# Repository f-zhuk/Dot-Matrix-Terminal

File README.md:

# Dot-Matrix-Terminal
Dot matrix printer driver board

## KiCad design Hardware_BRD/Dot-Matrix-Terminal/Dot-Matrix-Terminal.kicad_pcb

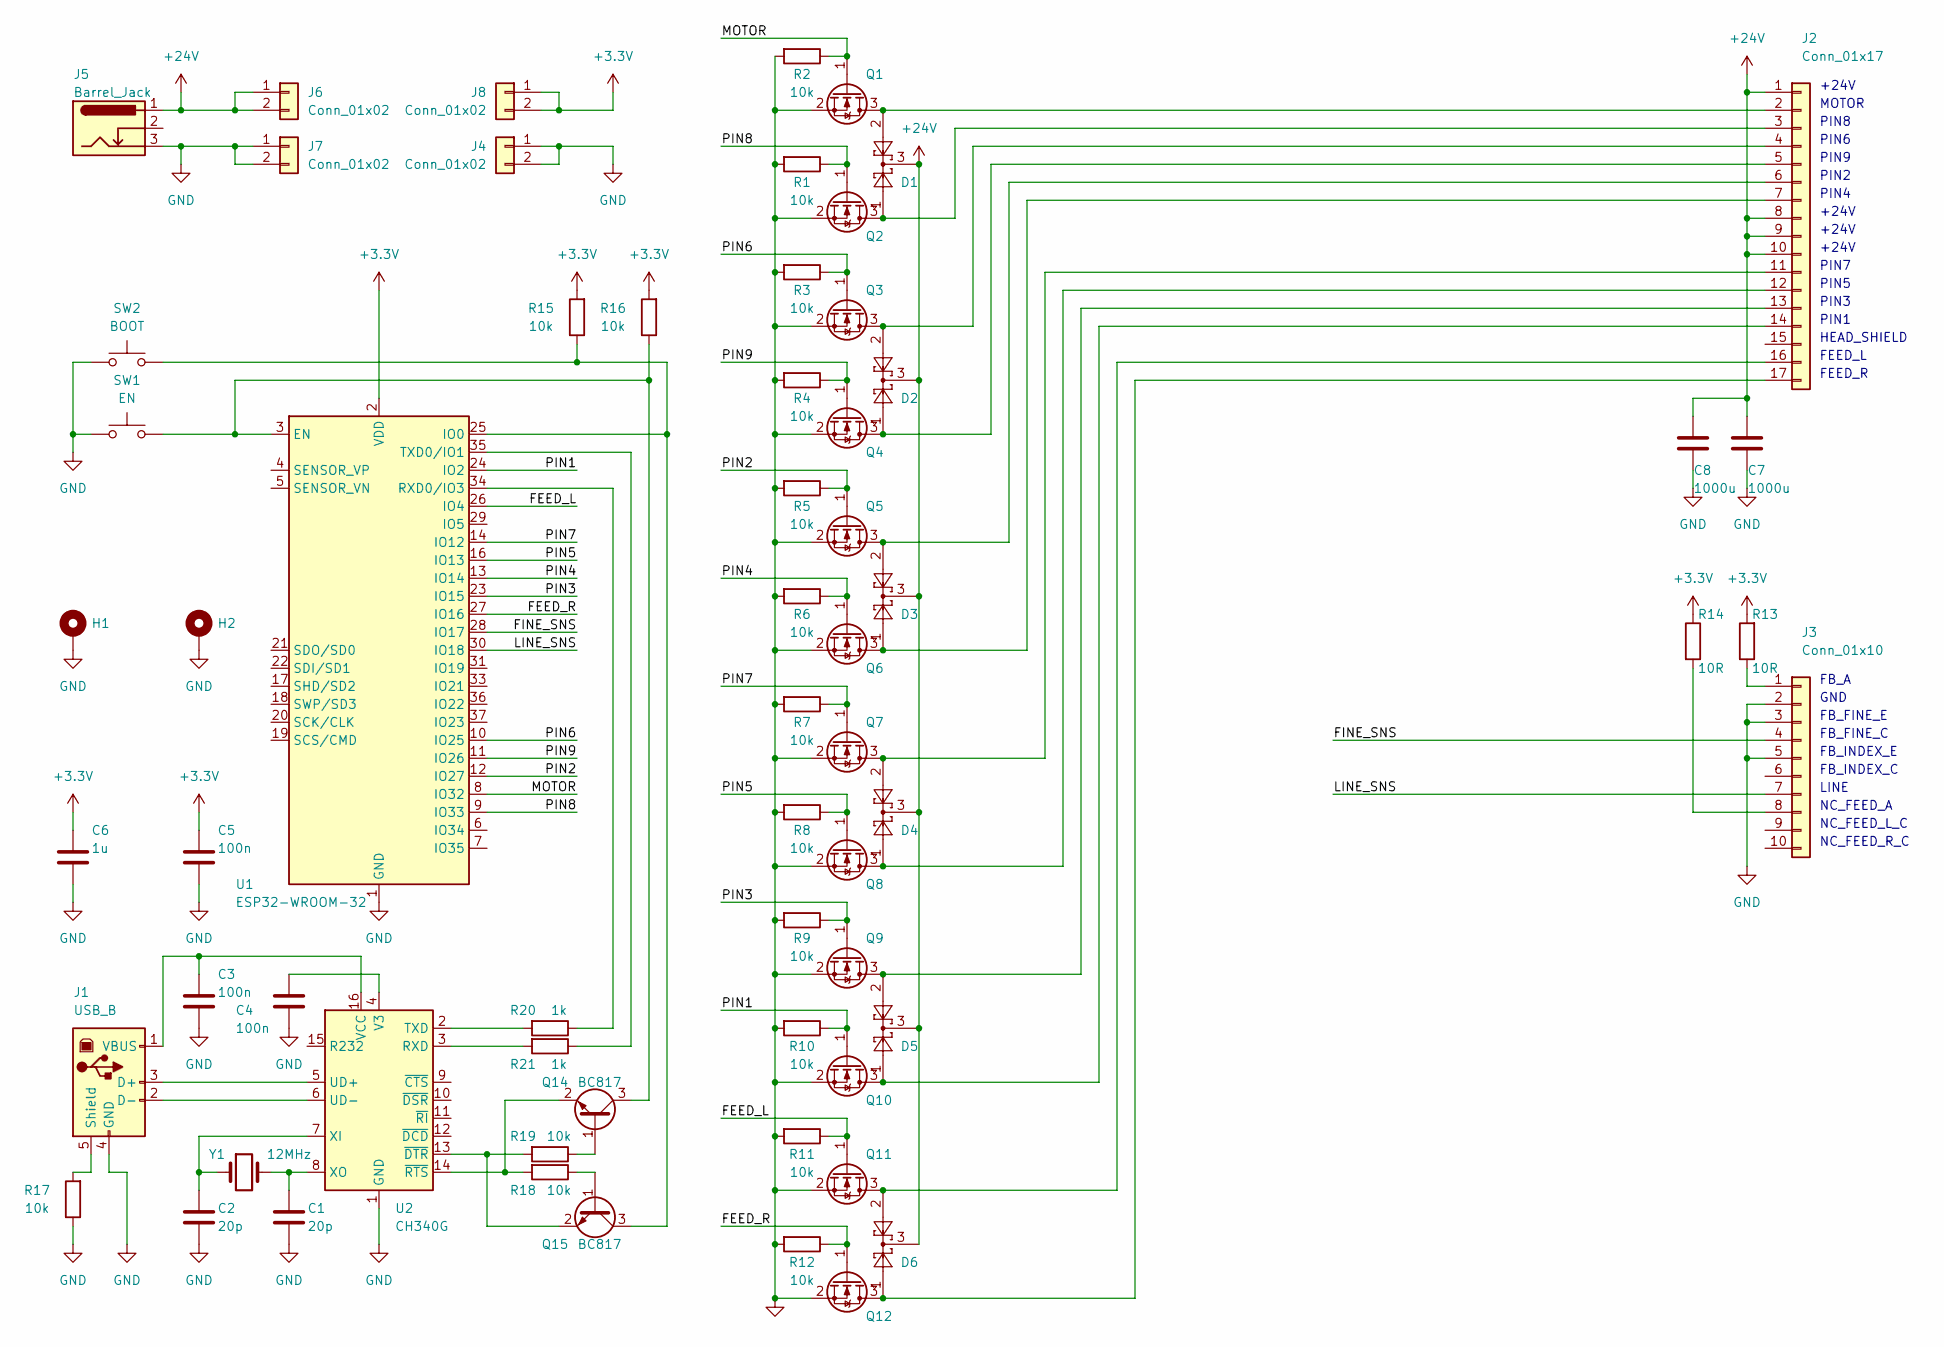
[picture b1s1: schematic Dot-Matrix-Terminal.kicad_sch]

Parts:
C1, C2: 20p; C_0603_1608Metric_Pad1.08x0.95mm_HandSolder
C3, C4, C5: 100n; C_0603_1608Metric_Pad1.08x0.95mm_HandSolder
C6: 1u; C_0603_1608Metric_Pad1.08x0.95mm_HandSolder
C7, C8: 1000u; C_Radial_D16.0mm_H25.0mm_P7.50mm
D1, D2, D3, D4, D5, D6: BAT54C; SOT-23_Handsoldering
H1, H2: MountingHole_Pad; MountingHole_3.2mm_M3_DIN965_Pad
J1: USB_B; USB_B_Lumberg_2411_02_Horizontal
J2: Conn_01x17; PinSocket_1x17_P2.54mm_Vertical
J3: Conn_01x10; PinSocket_1x10_P2.54mm_Vertical
J4, J6, J7, J8: Conn_01x02; PinHeader_1x02_P2.54mm_Vertical
J5: Barrel_Jack; BarrelJack_Horizontal
Q1, Q2, Q3, Q4, Q5, Q6, Q7, Q8, Q9, Q10, Q11, Q12: IRLML0030; SOT-23_Handsoldering
Q14, Q15: BC817; SOT-23_Handsoldering
R1, R2, R3, R4, R5, R6, R7, R8, R9, R10, R11, R12, R15, R16, R17, R18, R19: 10k; R_0603_1608Metric_Pad0.98x0.95mm_HandSolder
R13, R14: 10R; R_0603_1608Metric_Pad0.98x0.95mm_HandSolder
R20, R21: 1k; R_0603_1608Metric_Pad0.98x0.95mm_HandSolder
SW1: EN; SW_SPST_CK_PTS641
SW2: BOOT; SW_SPST_CK_PTS641
U1: ESP32-WROOM-32
U2: CH340G; SOIC-16_3.9x9.9mm_P1.27mm
Y1: 12MHz; Crystal_HC49-U_Vertical

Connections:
+3.3V: C5.1, C6.1, J8.1, J8.2, R13.2, R14.1, R15.2, R16.2, U1.2 (VDD)
+24V: C7.1, C8.1, D1.3, D2.3, D3.3, D4.3, D5.3, D6.3, J2.1, J2.8, J2.9, J2.10, J5.1, J6.1, J6.2
/FEED_L: Q11.1 (G), R11.1, U1.26 (IO4)
/FEED_R: Q12.1 (G), R12.1, U1.27 (IO16)
/FINE_SNS: J3.4, U1.28 (IO17)
/LINE_SNS: J3.7, U1.30 (IO18)
/MOTOR: Q1.1 (G), R2.1, U1.8 (IO32)
/PIN1: Q10.1 (G), R10.1, U1.24 (IO2)
/PIN2: Q5.1 (G), R5.1, U1.12 (IO27)
/PIN3: Q9.1 (G), R9.1, U1.23 (IO15)
/PIN4: Q6.1 (G), R6.1, U1.13 (IO14)
/PIN5: Q8.1 (G), R8.1, U1.16 (IO13)
/PIN6: Q3.1 (G), R3.1, U1.10 (IO25)
/PIN7: Q7.1 (G), R7.1, U1.14 (IO12)
/PIN8: Q2.1 (G), R1.1, U1.9 (IO33)
/PIN9: Q4.1 (G), R4.1, U1.11 (IO26)
GND: C1.2, C2.2, C3.2, C4.2, C5.2, C6.2, C7.2, C8.2, H1.1, H2.1, J1.4 (GND), J3.2, J3.3, J3.5, J4.1, J4.2, J5.3, J7.1, J7.2, Q1.2 (S), Q2.2 (S), Q3.2 (S), Q4.2 (S), Q5.2 (S), Q6.2 (S), Q7.2 (S), Q8.2 (S), Q9.2 (S), Q10.2 (S), Q11.2 (S), Q12.2 (S), R1.2, R2.2, R3.2, R4.2, R5.2, R6.2, R7.2, R8.2, R9.2, R10.2, R11.2, R12.2, R17.1, SW1.1, SW2.1, U1.1 (GND), U1.15 (GND), U1.38 (GND), U1.39 (GND), U2.1 (GND)
unnamed: J1.3 (D+), U2.5 (UD+)
unnamed: J1.2 (D-), U2.6 (UD-)
unnamed: J1.5 (Shield), R17.2
unnamed: C3.1, J1.1 (VBUS), U2.16 (VCC)
unnamed: D1.2, J2.2, Q1.3 (D)
unnamed: D1.1, J2.3, Q2.3 (D)
unnamed: D2.2, J2.4, Q3.3 (D)
unnamed: D2.1, J2.5, Q4.3 (D)
unnamed: D3.2, J2.6, Q5.3 (D)
unnamed: D3.1, J2.7, Q6.3 (D)
unnamed: D4.2, J2.11, Q7.3 (D)
unnamed: D4.1, J2.12, Q8.3 (D)
unnamed: D5.2, J2.13, Q9.3 (D)
unnamed: D5.1, J2.14, Q10.3 (D)
unnamed: D6.2, J2.16, Q11.3 (D)
unnamed: D6.1, J2.17, Q12.3 (D)
unnamed: J3.1, R13.1
unnamed: J3.8, R14.2
unnamed: Q14.1 (B), R19.1
unnamed: Q14.3 (C), R16.1, SW1.2, U1.3 (EN)
unnamed: Q14.2 (E), R18.2, U2.14 (~RTS)
unnamed: Q15.1 (B), R18.1
unnamed: Q15.3 (C), R15.1, SW2.2, U1.25 (IO0)
unnamed: Q15.2 (E), R19.2, U2.13 (~DTR)
unnamed: R20.1, U1.34 (RXD0/IO3)
unnamed: R21.1, U1.35 (TXD0/IO1)
unnamed: R21.2, U2.3 (RXD)
unnamed: R20.2, U2.2 (TXD)
unnamed: C4.1, U2.4 (V3)
unnamed: C2.1, U2.7 (XI), Y1.1
unnamed: C1.1, U2.8 (XO), Y1.2

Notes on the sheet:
FB_A
FB_INDEX_E
+24V
LINE
NC_FEED_L_C
HEAD_SHIELD
PIN3
FB_FINE_E
FB_FINE_C
NC_FEED_A
PIN1
PIN9
NC_FEED_R_C
FEED_L
PIN4
PIN6
PIN2
FB_INDEX_C
PIN5
PIN8
MOTOR
FEED_R
PIN7
GND

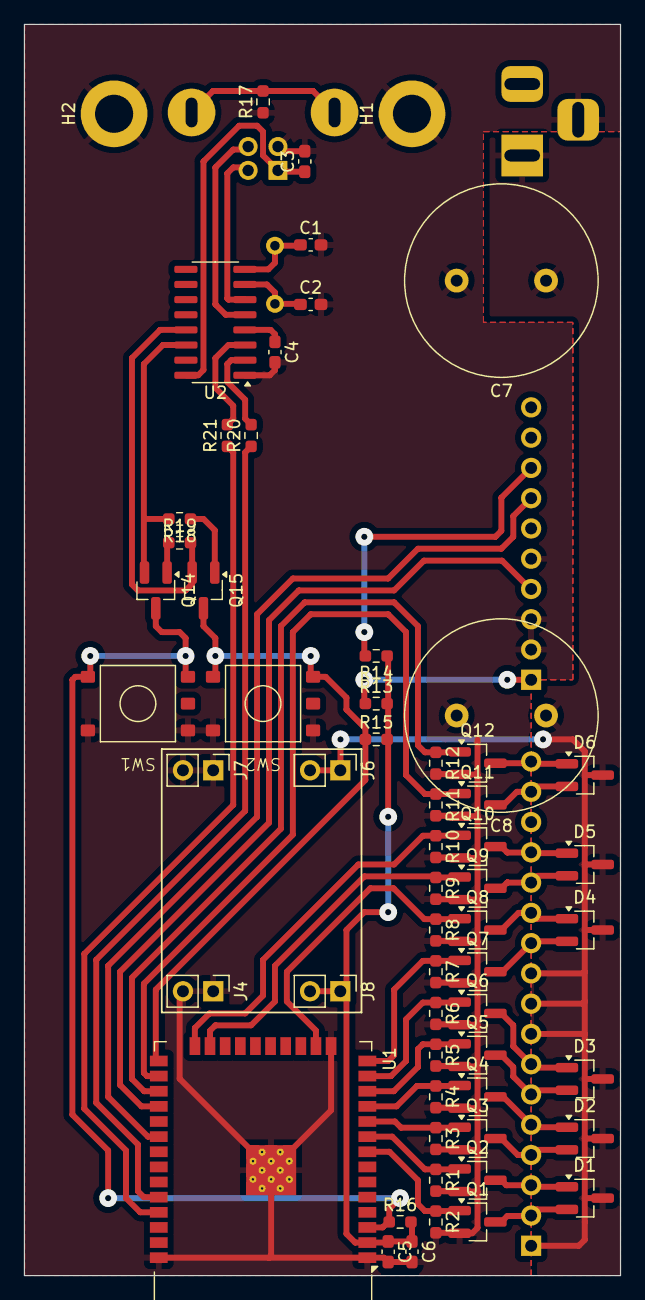
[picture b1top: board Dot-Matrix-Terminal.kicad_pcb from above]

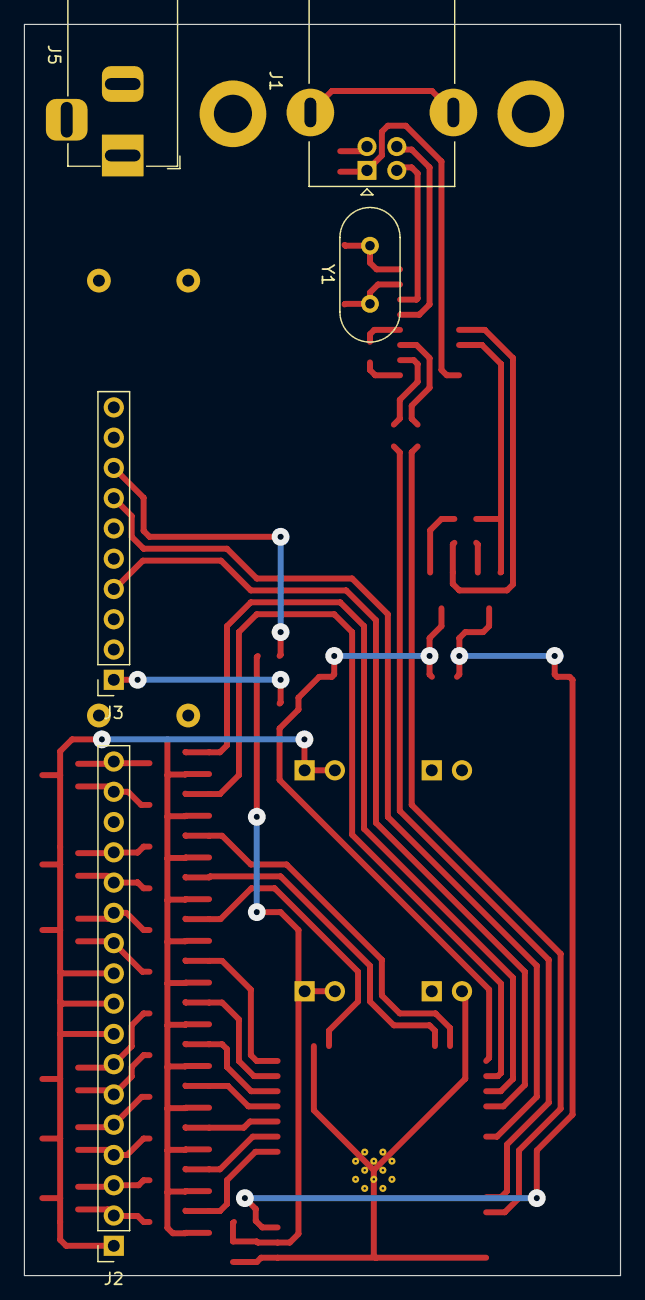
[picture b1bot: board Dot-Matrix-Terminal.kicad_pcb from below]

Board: 2 copper layers, 50.0 x 105.0 mm, 64 parts (5 on the bottom side), 48 nets.

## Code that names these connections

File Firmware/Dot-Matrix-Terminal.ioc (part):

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Mcu.Name=STM32F103C(8-B)Tx
Mcu.Package=LQFP48
Mcu.UserName=STM32F103C8Tx
PA13.Mode=Serial_Wire
PA13.Signal=SYS_JTMS-SWDIO
PA14.Mode=Serial_Wire
PA14.Signal=SYS_JTCK-SWCLK
PB10.Signal=S_TIM2_CH3
PB11.GPIOParameters=GPIO_PuPd,GPIO_Label,GPIO_ModeDefaultEXTI
PB11.GPIO_Label=OPTO
PB11.GPIO_ModeDefaultEXTI=GPIO_MODE_IT_RISING
PB11.GPIO_PuPd=GPIO_PULLUP
PB11.Signal=GPXTI11
PC13-TAMPER-RTC.GPIOParameters=GPIO_Label
PC13-TAMPER-RTC.GPIO_Label=LED
PC13-TAMPER-RTC.Signal=GPIO_Output
PC15-OSC32_OUT.GPIOParameters=GPIO_Label
PC15-OSC32_OUT.GPIO_Label=MTR
PC15-OSC32_OUT.Signal=GPIO_Output
PD0-OSC_IN.Mode=HSE-External-Oscillator
PD0-OSC_IN.Signal=RCC_OSC_IN
PD1-OSC_OUT.Mode=HSE-External-Oscillator
PD1-OSC_OUT.Signal=RCC_OSC_OUT
RCC.SYSCLKFreq_VALUE=72000000
RCC.SYSCLKSource=RCC_SYSCLKSOURCE_PLLCLK
board=custom

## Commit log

2024-03-03 Initial push
2024-03-04 Interrupt added
2024-06-16 Revived head's coils, got first ouput on the paper
2024-06-18 First usable result on paper
2024-07-20 The project retargeted at ESP-WROOM-32 module
2024-07-21 unsuccessful attempt at single layer routing
2024-07-21 MVP board
2024-07-22 First gerbers added
2024-07-22 Couple of mounting holes added
2024-07-23 Rotated board since FlatCAM can not do it properly(
2024-07-23 PCB CNC gcodes added
2024-07-23 gcodes reexported for grbl
2024-07-25 New DRL file
2024-07-25 Layer with slots added
2024-07-25 Slot mill nc generated (not added to the project)
2024-07-25 Slot layer lines thinned
2024-07-25 Included slot layer routing in the project
2024-07-25 Schematic PDF added for convenience
